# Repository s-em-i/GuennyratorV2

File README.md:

# GuennyratorV2

## Status
* In development

## License
* No License, open domain

## Johnson Counter (Train)
* [Texas Instruments CD74ACT175 Quad D-Type Flip-Flops with Reset](https://www.ti.com/product/CD74ACT175)
* [CMOS Dual J-K Master-Slave Flip-Flop](https://www.ti.com/product/CD4027B)

## Ring Counter
* [Texas Instruments CD74HC4017 High Speed CMOS Logic Decade Counter/Divider with 10 Decoded Outputs](https://www.ti.com/product/CD74HC4017)

## Direction Change
* [Texas Instruments CD74AC00 4-ch, 2-input, 1.5-V to 5.5-V NAND gates](https://www.ti.com/product/CD74AC00)

## Square Wave with 50% accurate Duty Cycle Frequency Generator
* [Texas Instruments TLC555 2.1-MHz, 250-µA, Low-Power Timer](https://www.ti.com/product/TLC555)

## Mechanical Setup
* [STATOR TRIUMPH 955(i)](https://www.rmstator-europe.com/en/955-tiger-/310-stator-triumph-speed-triple-955-sprint-rs-955-sprint-st-955-tiger-955-oem-t1300502-t1300350.html)
	- Dimensions :
		- Interior diameter : 41 mm 
		- Exterior diameter : 104 mm 
		- Thickness : 22 mm
* [AS-PL Alternator stator AS2002](https://as-pl.com/en/p/AS2002)
	- Dimensions :
		- I.D.1 [ mm ]	104.30
		- H.2 [ mm ]	22.10
* [AS-PL Alternator A2005](https://as-pl.com/en/p/A2005)

## Signalgenerator (PLL)
* [XR2206 Multi-Function Generator](https://www.uctronics.com/download/Amazon/U6035.pdf)
* [ICL8038](https://www.delabs-circuits.com/cirdir/hobby/test-tools/del50005.html)
* [Texas Instruments CD4060B CMOS 14-Stage Ripple-Carry Binary Counter/Divider and Oscillator](https://www.ti.com/product/CD4060B)
* [Texas Instruments SN74HC4060-Q1 ACTIVE Automotive Catalog 14-Stage Asynchronous Binary Counters And Oscillators](https://www.ti.com/product/SN74HC4060-Q1)

### Credits
* [Schematics Simulated with Analog Devices LTspice](https://www.analog.com/en/design-center/design-tools-and-calculators/ltspice-simulator.html)
* [Schematics Designed with KiCad EDA](https://www.kicad.org)
* [USING CD4000_V.LIB AND 74HC.LIB IN LTSPICE by acidbourbon](https://acidbourbon.wordpress.com/2021/06/30/using-cd4000_v-lib-in-ltspice/)
* [Logisim by carlburch](https://sourceforge.net/projects/circuit/)
* [TEXMAKER - LaTex](https://www.xm1math.net/texmaker/download.html)
* [Alexander Baran-Harper - Latex Tutorials](https://www.youtube.com/watch?v=FXujG7c9p8g&list=PLNnwglGGYoTtW7o4PHFOSWGevcdFa3v3D)
* [Michelle Krummel  - Latex Tutorials](https://www.youtube.com/watch?v=0ivLZh9xK1Q&list=PL1D4EAB31D3EBC449)

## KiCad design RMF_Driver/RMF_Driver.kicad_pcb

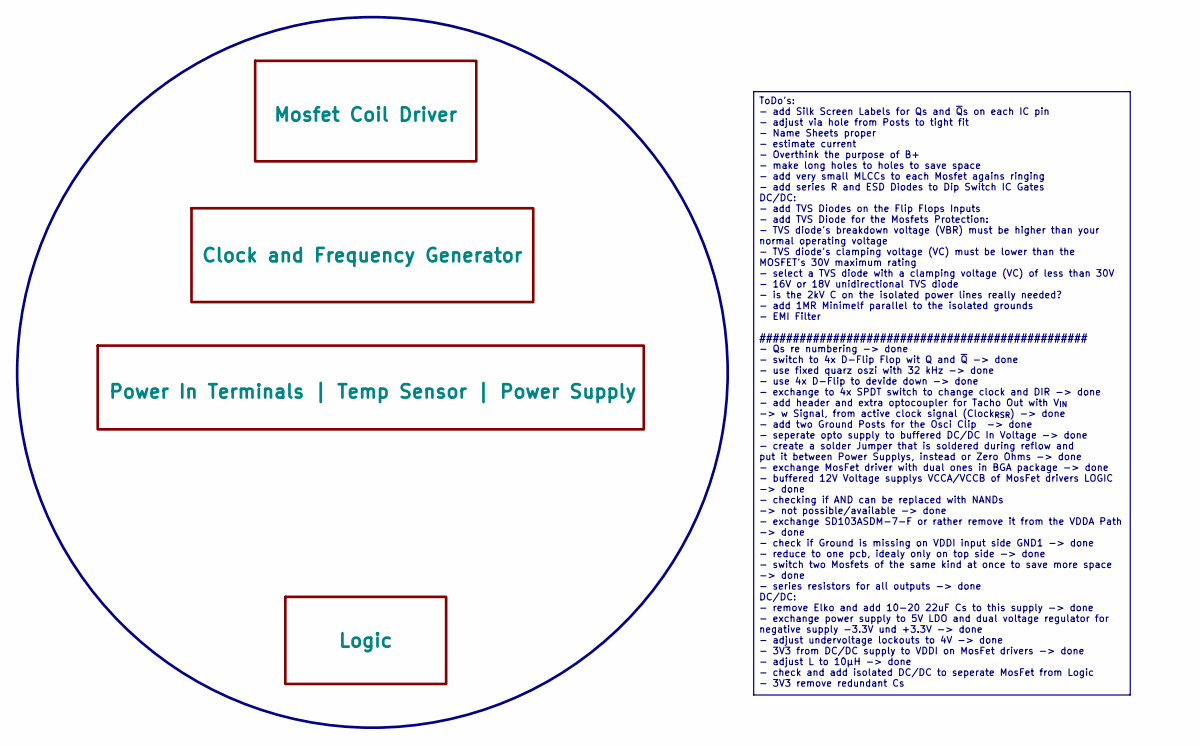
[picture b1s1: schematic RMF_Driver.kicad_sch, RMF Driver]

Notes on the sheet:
ToDo's: - add Silk Screen Labels for Qs and ~{Q}s on each IC pin - adjust via hole from Posts to tight fit - Name Sheets proper - estimate current - Overthink the purpose of B+ - make long holes to holes to save space - add very small MLCCs to each Mosfet agains ringing - add series R and ESD Diode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

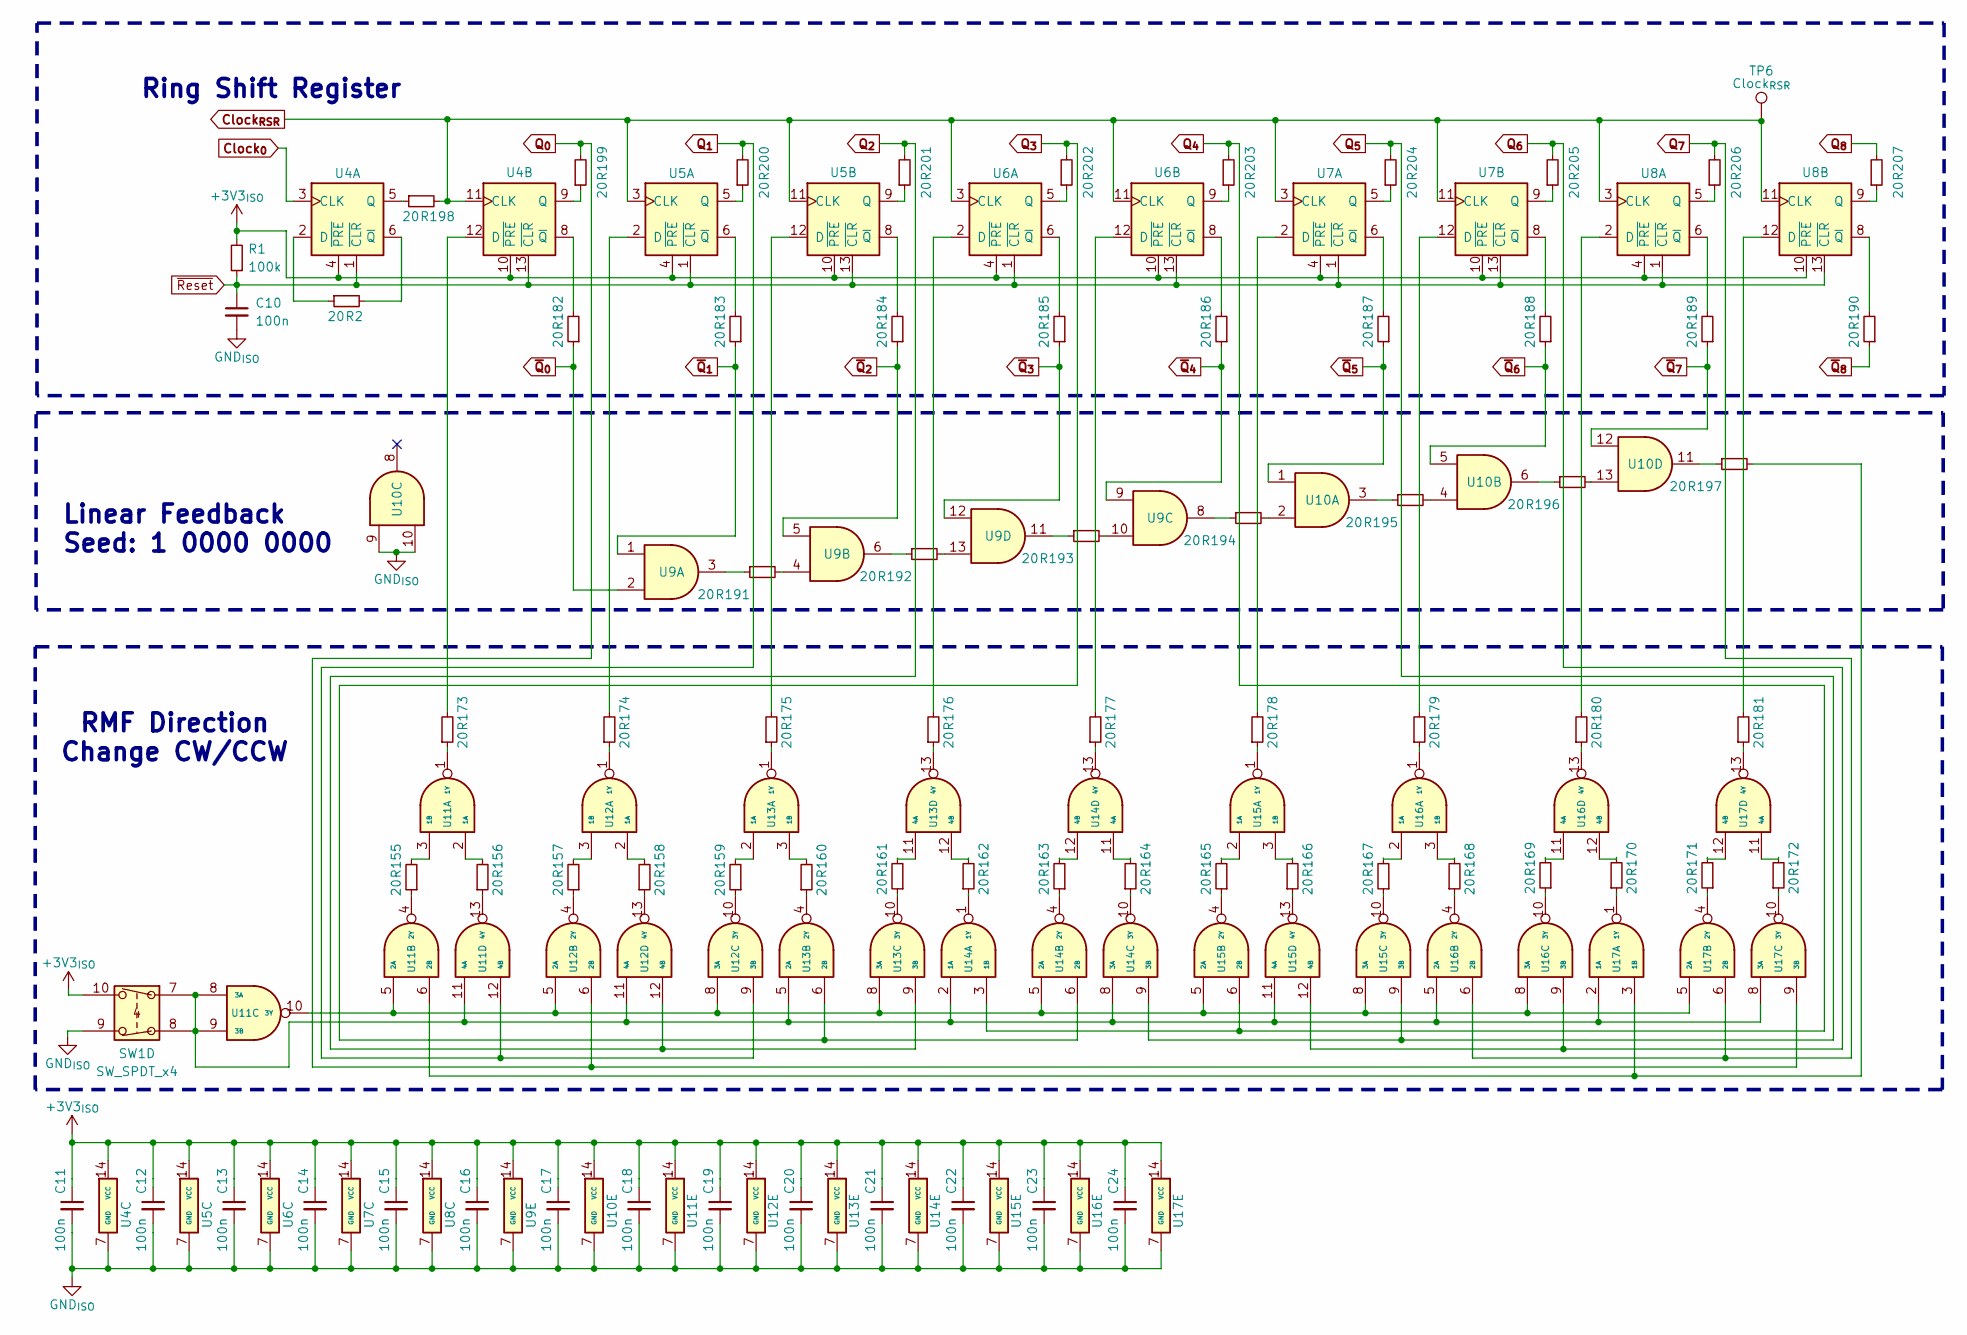
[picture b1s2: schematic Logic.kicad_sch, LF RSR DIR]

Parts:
C10, C11, C12, C13, C14, C15, C16, C17, C18, C19, C20, C21, C22, C23, C24: 100n; C_0402_1005Metric; MPN 1 CL05B104KB54PNC
R1: 100k; R_0402_1005Metric; MPN 1 AC0402FR-13100KL
R2, R155, R156, R157, R158, R159, R160, R161, R162, R163, R164, R165, R166, R167, R168, R169, R170, R171, R172, R173, R174, R175, R176, R177, R178, R179, R180, R181, R182, R183, R184, R185, R186, R187, R188, R189, R190, R191, R192, R193, R194, R195, R196, R197, R198, R199, R200, R201, R202, R203, R204, R205, R206, R207: 20; R_0402_1005Metric; MPN 1 AC0402FR-0720RL
SW1: SW_SPDT_x4; CTS_204-124; MPN 1 204-124LPST
TP6: Clock_{RSR}; 243-131; MPN 1 243-131
U4, U5, U6, U7, U8: D-FF; DHVQFN-14-1EP_2.5x3mm_P0.5mm_EP1x1.5mm
U9, U10: AND; WQFN-14-1EP_2.6x3.1mm_P0.5mm_EP1.1x1.6mm_ThermalVias; MPN 1 SN74AHC08QWBQARQ1
U11, U12, U13, U14, U15, U16, U17: NAND; WQFN-14-1EP_2.6x3.1mm_P0.5mm_EP1.1x1.6mm_ThermalVias; MPN 1 SN74AHC00BQAR

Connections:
+3V3_{ISO}: C11.1, C12.1, C13.1, C14.1, C15.1, C16.1, C17.1, C18.1, C19.1, C20.1, C21.1, C22.1, C23.1, C24.1, R1.2, SW1.10 (D), U4.4 (~PRE), U4.10 (~PRE), U4.14 (VCC), U5.4 (~PRE), U5.10 (~PRE), U5.14 (VCC), U6.4 (~PRE), U6.10 (~PRE), U6.14 (VCC), U7.4 (~PRE), U7.10 (~PRE), U7.14 (VCC), U8.4 (~PRE), U8.10 (~PRE), U8.14 (VCC), U9.14 (VCC), U10.14 (VCC), U11.14 (VCC), U12.14 (VCC), U13.14 (VCC), U14.14 (VCC), U15.14 (VCC), U16.14 (VCC), U17.14 (VCC); also elsewhere on the board
Clock_{0}: U4.3 (CLK); also elsewhere on the board
Clock_{RSR}: R198.2, TP6.1 (1_1), U4.11 (CLK), U5.3 (CLK), U5.11 (CLK), U6.3 (CLK), U6.11 (CLK), U7.3 (CLK), U7.11 (CLK), U8.3 (CLK), U8.11 (CLK); also elsewhere on the board
GND_{ISO}: C10.2, C11.2, C12.2, C13.2, C14.2, C15.2, C16.2, C17.2, C18.2, C19.2, C20.2, C21.2, C22.2, C23.2, C24.2, SW1.9 (C), U4.7 (GND), U4.15 (PAD), U5.7 (GND), U5.15 (PAD), U6.7 (GND), U6.15 (PAD), U7.7 (GND), U7.15 (PAD), U8.7 (GND), U8.15 (PAD), U9.7 (GND), U9.15 (GND), U10.7 (GND), U10.9, U10.10, U10.15 (GND), U11.7 (GND), U11.15 (GND), U12.7 (GND), U12.15 (GND), U13.7 (GND), U13.15 (GND), U14.7 (GND), U14.15 (GND), U15.7 (GND), U15.15 (GND), U16.7 (GND), U16.15 (GND), U17.7 (GND), U17.15 (GND); also elsewhere on the board
unnamed: R191.1, U9.3
unnamed: R191.2, U9.4
unnamed: R192.1, U9.6
unnamed: R192.2, U9.13
unnamed: R193.1, U9.11
unnamed: R193.2, U9.10
unnamed: R194.1, U9.8
unnamed: R194.2, U10.2
unnamed: R195.1, U10.3
unnamed: R195.2, U10.4
unnamed: R196.1, U10.6
unnamed: R196.2, U10.13
unnamed: R197.1, U10.11
unnamed: SW1.7 (A), SW1.8 (B), U11.8 (3A), U11.9 (3B), U11.11 (4A), U12.11 (4A), U13.5 (2A), U14.2 (1A), U14.8 (3A), U15.11 (4A), U16.5 (2A), U17.2 (1A), U17.8 (3A)
unnamed: R2.1, U4.2 (D)
unnamed: R198.1, U4.5 (Q)
unnamed: R2.2, U4.6 (~Q)
unnamed: R173.2, U4.12 (D)
unnamed: R199.1, U4.9 (Q)
unnamed: R182.2, U4.8 (~Q)
unnamed: R174.2, U5.2 (D)
unnamed: R200.1, U5.5 (Q)
unnamed: R183.2, U5.6 (~Q)
unnamed: R175.2, U5.12 (D)
unnamed: R201.1, U5.9 (Q)
unnamed: R184.2, U5.8 (~Q)
unnamed: R176.2, U6.2 (D)
unnamed: R202.1, U6.5 (Q)
unnamed: R185.2, U6.6 (~Q)
unnamed: R177.2, U6.12 (D)
unnamed: R203.1, U6.9 (Q)
unnamed: R186.2, U6.8 (~Q)
unnamed: R178.2, U7.2 (D)
unnamed: R204.1, U7.5 (Q)
unnamed: R187.2, U7.6 (~Q)
unnamed: R179.2, U7.12 (D)
unnamed: R205.1, U7.9 (Q)
unnamed: R188.2, U7.8 (~Q)
unnamed: R180.2, U8.2 (D)
unnamed: R206.1, U8.5 (Q)
unnamed: R189.2, U8.6 (~Q)
unnamed: R181.2, U8.12 (D)
unnamed: R207.1, U8.9 (Q)
unnamed: R190.2, U8.8 (~Q)
unnamed: R156.2, U11.2 (1A)
unnamed: R155.2, U11.3 (1B)
unnamed: R173.1, U11.1 (1Y)
unnamed: U11.5 (2A), U11.10 (3Y), U12.5 (2A), U12.8 (3A), U13.8 (3A), U14.5 (2A), U15.5 (2A), U15.8 (3A), U16.8 (3A), U17.5 (2A)
unnamed: R197.2, U11.6 (2B), U17.3 (1B)
unnamed: R155.1, U11.4 (2Y)
unnamed: R156.1, U11.13 (4Y)
unnamed: R158.2, U12.2 (1A)
unnamed: R157.2, U12.3 (1B)
unnamed: R174.1, U12.1 (1Y)
unnamed: R157.1, U12.4 (2Y)
unnamed: R159.1, U12.10 (3Y)
unnamed: R158.1, U12.13 (4Y)
unnamed: R159.2, U13.2 (1A)
unnamed: R160.2, U13.3 (1B)
unnamed: R175.1, U13.1 (1Y)
unnamed: R160.1, U13.4 (2Y)
unnamed: R161.1, U13.10 (3Y)
unnamed: R161.2, U13.11 (4A)
unnamed: R162.2, U13.12 (4B)
unnamed: R176.1, U13.13 (4Y)
unnamed: R162.1, U14.1 (1Y)
unnamed: R163.1, U14.4 (2Y)
unnamed: R164.1, U14.10 (3Y)
unnamed: R164.2, U14.11 (4A)
unnamed: R163.2, U14.12 (4B)
unnamed: R177.1, U14.13 (4Y)
unnamed: R165.2, U15.2 (1A)
unnamed: R166.2, U15.3 (1B)
unnamed: R178.1, U15.1 (1Y)
unnamed: R165.1, U15.4 (2Y)
unnamed: R167.1, U15.10 (3Y)
unnamed: R166.1, U15.13 (4Y)
unnamed: R167.2, U16.2 (1A)
unnamed: R168.2, U16.3 (1B)
unnamed: R179.1, U16.1 (1Y)
unnamed: R168.1, U16.4 (2Y)
unnamed: R169.1, U16.10 (3Y)
unnamed: R169.2, U16.11 (4A)
unnamed: R170.2, U16.12 (4B)
unnamed: R180.1, U16.13 (4Y)
unnamed: R170.1, U17.1 (1Y)
unnamed: R171.1, U17.4 (2Y)
unnamed: R172.1, U17.10 (3Y)
unnamed: R172.2, U17.11 (4A)
unnamed: R171.2, U17.12 (4B)
unnamed: R181.1, U17.13 (4Y)
Q_{0}: R199.2, U12.6 (2B), U17.9 (3B); also elsewhere on the board
Q_{1}: R200.2, U11.12 (4B), U12.9 (3B); also elsewhere on the board
Q_{2}: R201.2, U12.12 (4B), U13.9 (3B); also elsewhere on the board
Q_{3}: R202.2, U13.6 (2B), U14.6 (2B); also elsewhere on the board
Q_{4}: R203.2, U14.3 (1B), U15.6 (2B); also elsewhere on the board
Q_{5}: R204.2, U14.9 (3B), U15.9 (3B); also elsewhere on the board
Q_{6}: R205.2, U15.12 (4B), U16.9 (3B); also elsewhere on the board
Q_{7}: R206.2, U16.6 (2B), U17.6 (2B); also elsewhere on the board
Q_{8}: R207.2; also elsewhere on the board
~Q_{0}: R182.1, U9.2; also elsewhere on the board
~Q_{1}: R183.1, U9.1; also elsewhere on the board
~Q_{2}: R184.1, U9.5; also elsewhere on the board
~Q_{3}: R185.1, U9.12; also elsewhere on the board
~Q_{4}: R186.1, U9.9; also elsewhere on the board
~Q_{5}: R187.1, U10.1; also elsewhere on the board
~Q_{6}: R188.1, U10.5; also elsewhere on the board
~Q_{7}: R189.1, U10.12; also elsewhere on the board
~Q_{8}: R190.1; also elsewhere on the board
~Reset: C10.1, R1.1, U4.1 (~CLR), U4.13 (~CLR), U5.1 (~CLR), U5.13 (~CLR), U6.1 (~CLR), U6.13 (~CLR), U7.1 (~CLR), U7.13 (~CLR), U8.1 (~CLR), U8.13 (~CLR); also elsewhere on the board

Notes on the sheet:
Ring Shift Register
RMF Direction Change CW/CCW
Linear Feedback Seed: 1 0000 0000

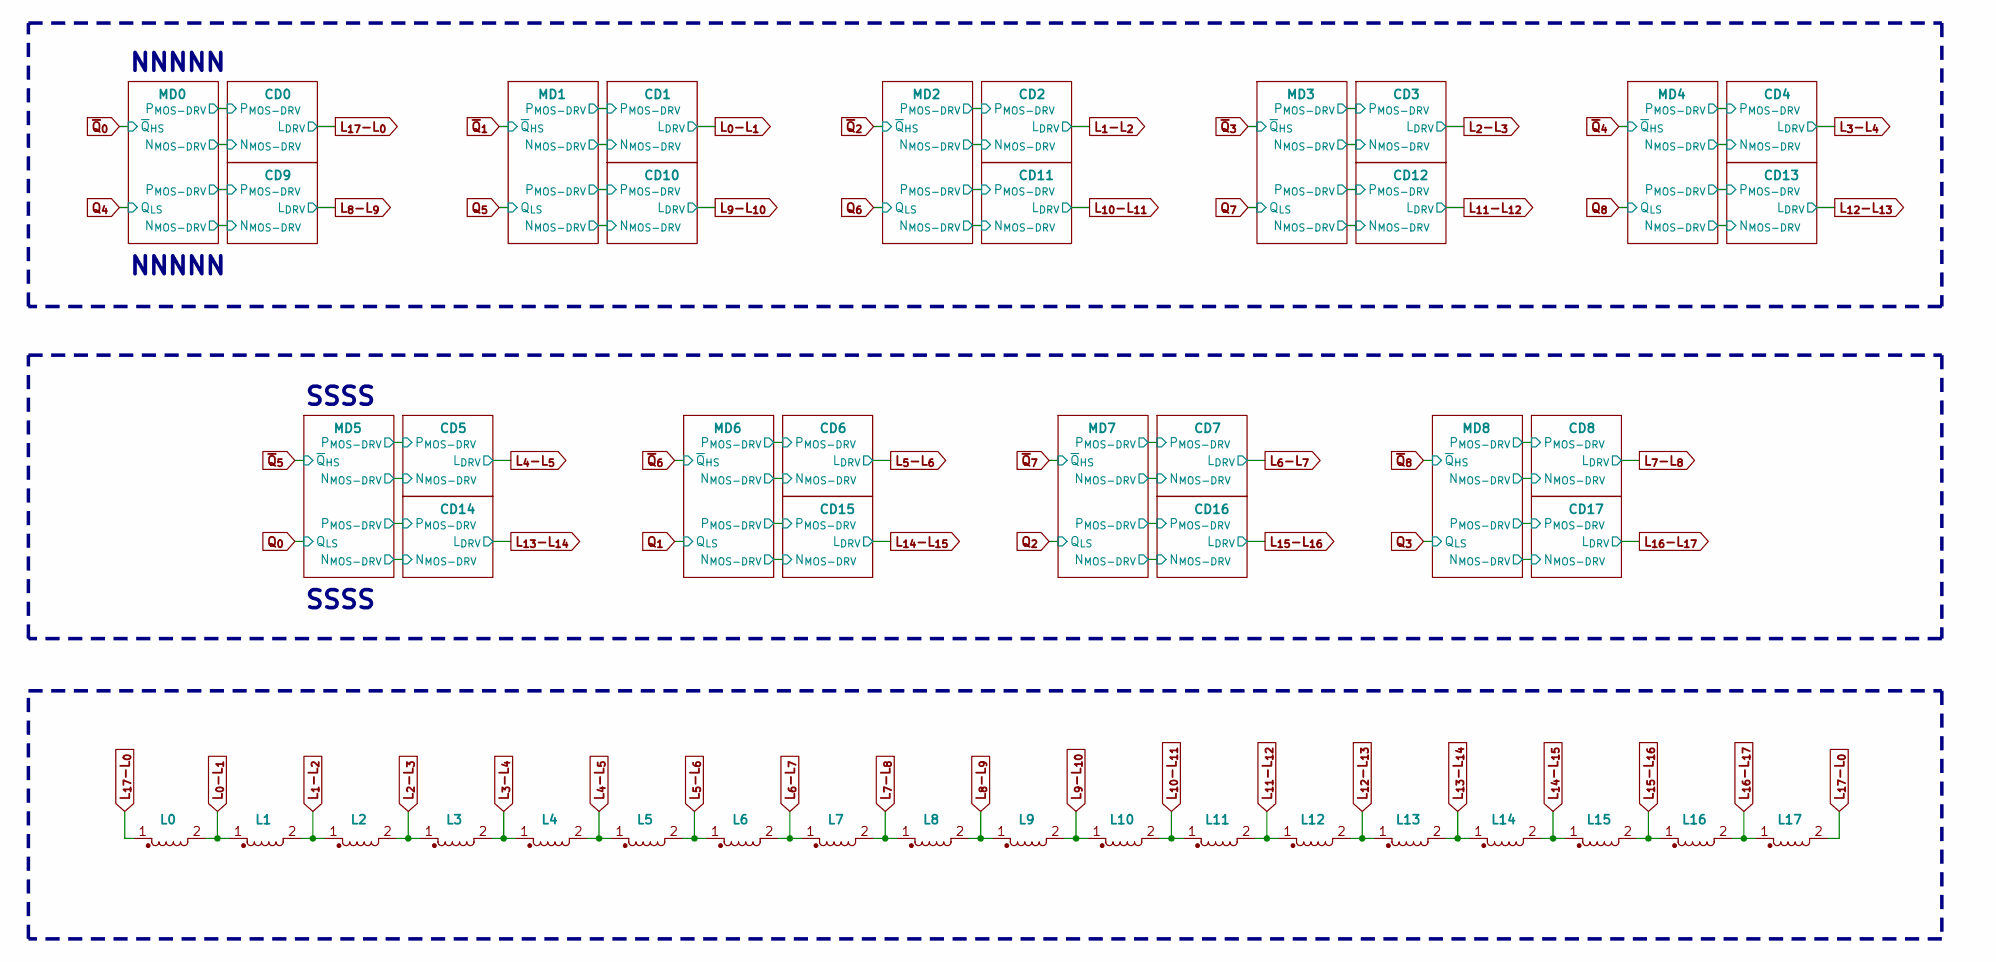
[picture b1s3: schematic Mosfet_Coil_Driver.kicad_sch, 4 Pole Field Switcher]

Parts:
L0, L1, L2, L3, L4, L5, L6, L7, L8, L9, L10, L11, L12, L13, L14, L15, L16, L17: L

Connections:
unnamed: L0.1, L17.2
unnamed: L0.2, L1.1
unnamed: L1.2, L2.1
unnamed: L2.2, L3.1
unnamed: L3.2, L4.1
unnamed: L4.2, L5.1
unnamed: L5.2, L6.1
unnamed: L6.2, L7.1
unnamed: L7.2, L8.1
unnamed: L8.2, L9.1
unnamed: L9.2, L10.1
unnamed: L10.2, L11.1
unnamed: L11.2, L12.1
unnamed: L12.2, L13.1
unnamed: L13.2, L14.1
unnamed: L14.2, L15.1
unnamed: L15.2, L16.1
unnamed: L16.2, L17.1

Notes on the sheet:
NNNNN
SSSS

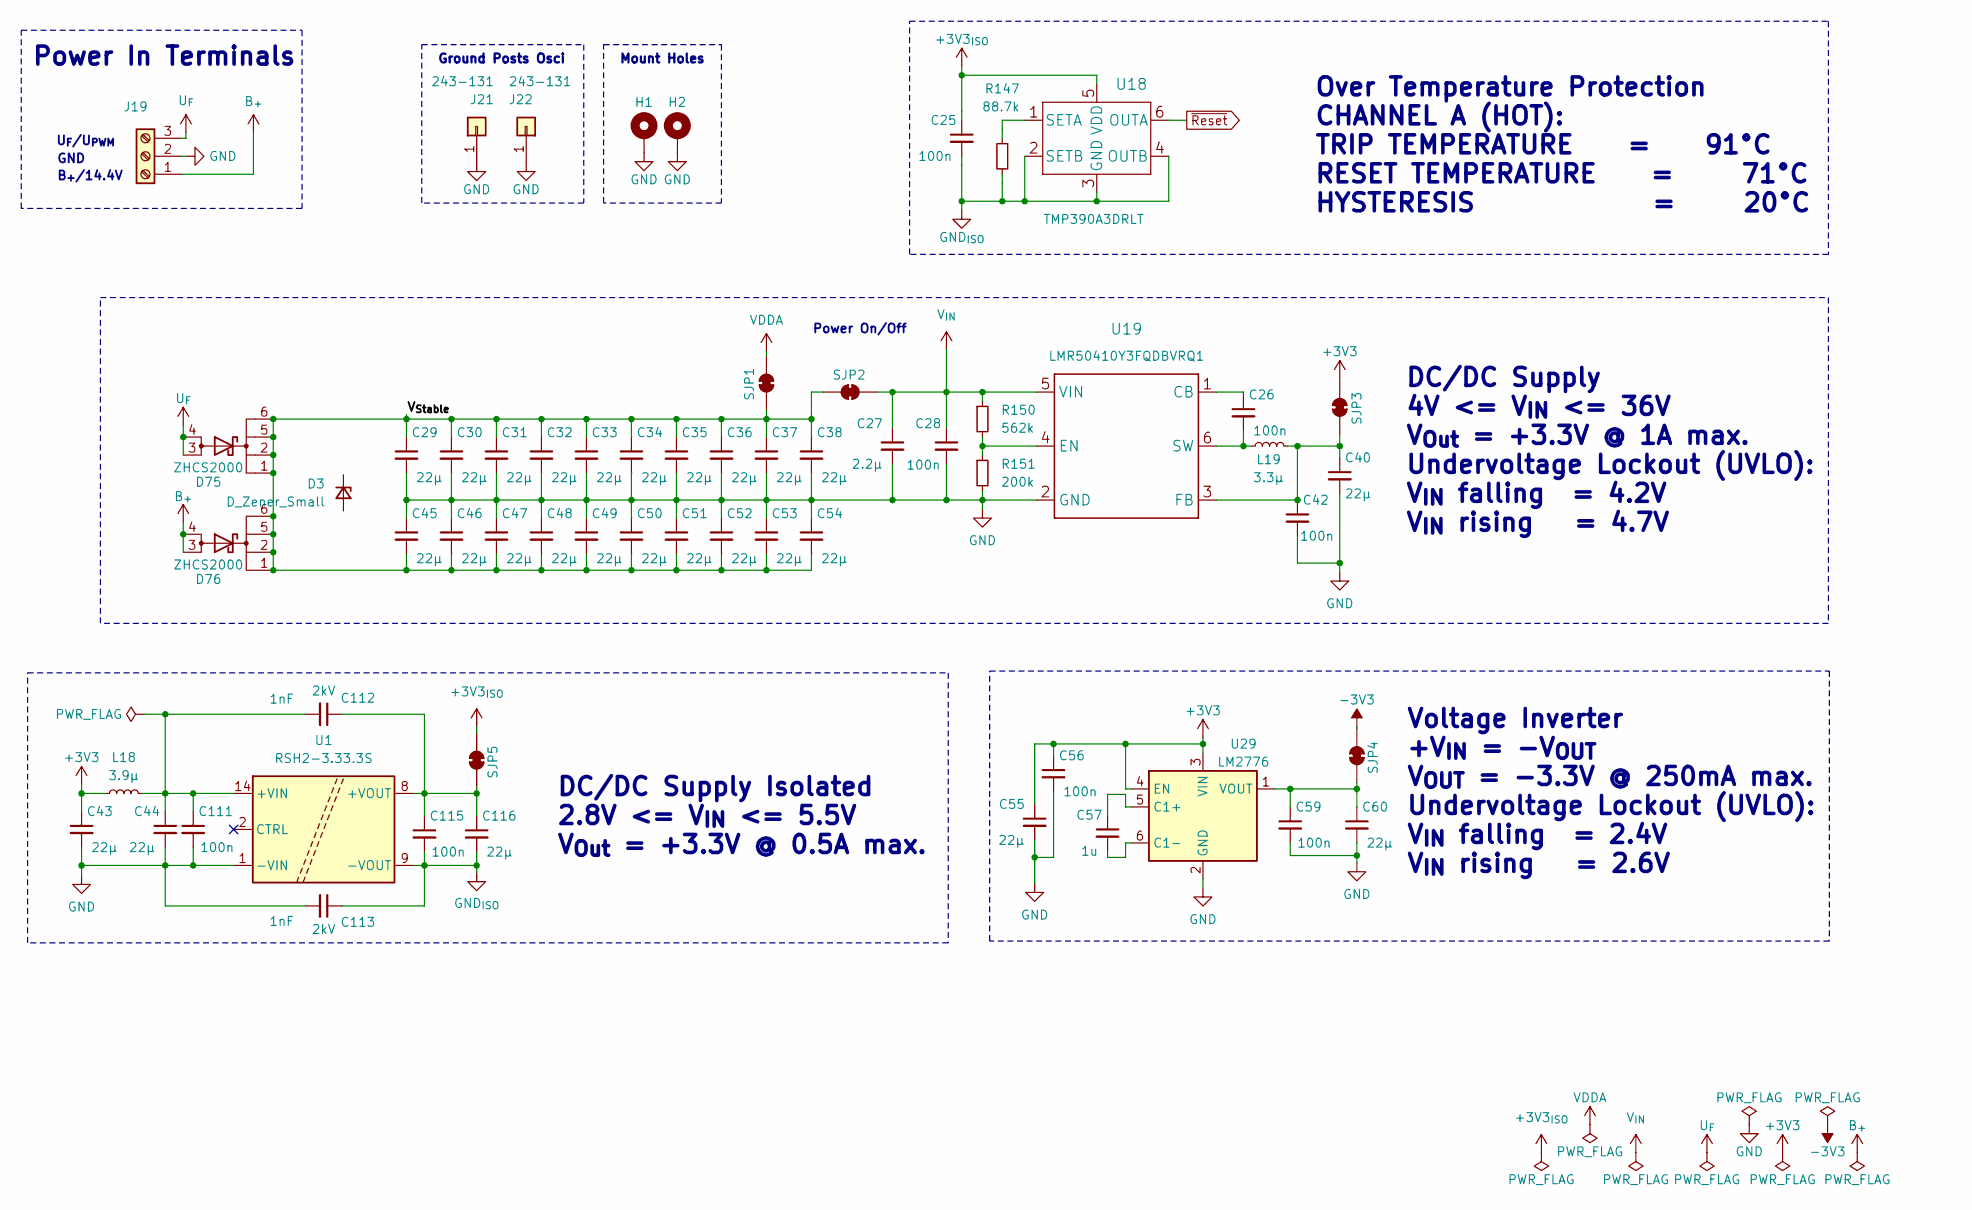
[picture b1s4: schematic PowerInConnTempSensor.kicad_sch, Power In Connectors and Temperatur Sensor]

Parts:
C25, C26, C28, C42, C56, C59, C111, C115: 100n; C_0402_1005Metric; MPN 1 CL05B104KB54PNC
C27: 2.2µ; C_0805_2012Metric; MPN 1 CL21B225KBYNNWE
C29, C30, C31, C32, C33, C34, C35, C36, C37, C38, C45, C46, C47, C48, C49, C50, C51, C52, C53, C54: 22µ; C_1210_3225Metric; MPN 1 CL32B226KAJNNNE
C40, C43, C44, C55, C60, C116: 22µ; C_0805_2012Metric; MPN 1 GRM21BZ71A226ME15L
C57: 1u; C_0603_1608Metric; MPN 1 CL10B105KB8NQNC
C112, C113: 1nF; C_1206_3216Metric; Voltage 2kV; MPN 1 C1206C102KGRAC
D3: D_Zener_Small
D75, D76: ZHCS2000; SOT-23-6; MPN 1 ZHCS2000
H1, H2: MountingHole_Pad; MountingHole_6.4mm_M6_ISO7380_Pad_TopBottom
J19: Screw_Terminal_01x03; PHOENIX_1984950; MPN 1 1984950
J21, J22: 243-131; MPN 1 243-131
L18: 3.9µ; L_Recom_RLS-397_4.5x3.2mm; MPN 1 RLS-397
L19: 3.3µ; WE-LHMI_4020; MPN 1 74437324033
R147: 88.7k; R_0603_1608Metric; MPN 1 RC0603FR-0788K7L
R150: 562k; R_0603_1608Metric; MPN 1 RC0603FR-07562KL
R151: 200k; R_0603_1608Metric; MPN 1 AC0603FR-07200KL
SJP1, SJP2, SJP3, SJP4, SJP5: SolderJumper_2_Bridged; SolderJumper-2_P1.3mm_Open_TrianglePad1.0x1.5mm
U1: RSH2-3.33.3S; RSH2; MPN 1 RSH2-3.33.3S
U18: TMP390A3DRLT; MPN 1 TMP390A3DRLT
U19: LMR50410Y3FQDBVRQ1; PLMR50410XDBVR; MPN 1 LMR50410Y3FQDBVRQ1
U29: LM2776; SOT-23-6

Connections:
+3V3: C43.1, C55.1, C56.1, L18.1, SJP3.2 (B), U29.3 (VIN), U29.4 (EN)
+3V3_{ISO}: C25.1, SJP5.2 (B), U18.5 (VDD); also elsewhere on the board
-3V3: SJP4.2 (B); also elsewhere on the board
/Power In Terminals | Temp Sensor | Power Supply/V_{Stable}: C29.1, C30.1, C31.1, C32.1, C33.1, C34.1, C35.1, C36.1, C37.1, C38.1, C45.2, C46.2, C47.2, C48.2, C49.2, C50.2, C51.2, C52.2, C53.2, C54.2, D75.1 (K), D75.2 (K), D75.5 (K), D75.6 (K), D76.1 (K), D76.2 (K), D76.5 (K), D76.6 (K), SJP1.1 (A), SJP2.1 (A)
B_{+}: D76.3 (A), D76.4 (A), J19.1
GND: C27.2, C28.2, C29.2, C30.2, C31.2, C32.2, C33.2, C34.2, C35.2, C36.2, C37.2, C38.2, C40.2, C42.2, C43.2, C44.2, C45.1, C46.1, C47.1, C48.1, C49.1, C50.1, C51.1, C52.1, C53.1, C54.1, C55.2, C56.2, C59.2, C60.2, C111.2, C113.2, H1.1 (1_1), H2.1 (1_1), J19.2, J21.1 (Pin_1_1), J22.1 (Pin_1_1), R151.2, U1.1 (-VIN), U1.6 (-VIN), U1.7 (-VIN), U19.2 (GND), U29.2 (GND); also elsewhere on the board
GND_{ISO}: C25.2, C113.1, C115.2, C116.2, R147.2, U1.9 (-VOUT), U18.2 (SETB), U18.3 (GND), U18.4 (OUTB); also elsewhere on the board
unnamed: C40.1, C42.1, L19.1, SJP3.1 (A), U19.3 (FB)
unnamed: C59.1, C60.1, SJP4.1 (A), U29.1 (VOUT)
unnamed: C112.1, C115.1, C116.1, SJP5.1 (A), U1.8 (+VOUT)
unnamed: C44.1, C111.1, C112.2, L18.2, U1.14 (+VIN)
unnamed: R147.1, U18.1 (SETA)
unnamed: C26.1, U19.1 (CB)
unnamed: R150.2, R151.1, U19.4 (EN)
unnamed: C26.2, L19.2, U19.6 (SW)
unnamed: C57.1, U29.5 (C1+)
unnamed: C57.2, U29.6 (C1-)
U_{F}: D75.3 (A), D75.4 (A), J19.3; also elsewhere on the board
VDDA: SJP1.2 (B); also elsewhere on the board
V_{IN}: C27.1, C28.1, R150.1, SJP2.2 (B), U19.5 (VIN)
~Reset: U18.6 (OUTA); also elsewhere on the board

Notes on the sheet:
Power On/Off
Power In Terminals
Over Temperature Protection CHANNEL A (HOT): TRIP TEMPERATURE = 91°C RESET TEMPERATURE = 71°C HYSTERESIS = 20°C
DC/DC Supply 4V <= V_{IN} <= 36V V_{Out} = +3.3V @ 1A max. Undervoltage Lockout (UVLO): V_{IN} falling = 4.2V V_{IN} rising = 4.7V
Mount Holes
Voltage Inverter +V_{IN} = -V_{OUT} V_{OUT} = -3.3V @ 250mA max. Undervoltage Lockout (UVLO): V_{IN} falling = 2.4V V_{IN} rising = 2.6V
DC/DC Supply Isolated 2.8V <= V_{IN} <= 5.5V V_{Out} = +3.3V @ 0.5A max.
GND
Ground Posts Osci
U_{F}/U_{PWM}
B_{+}/14.4V

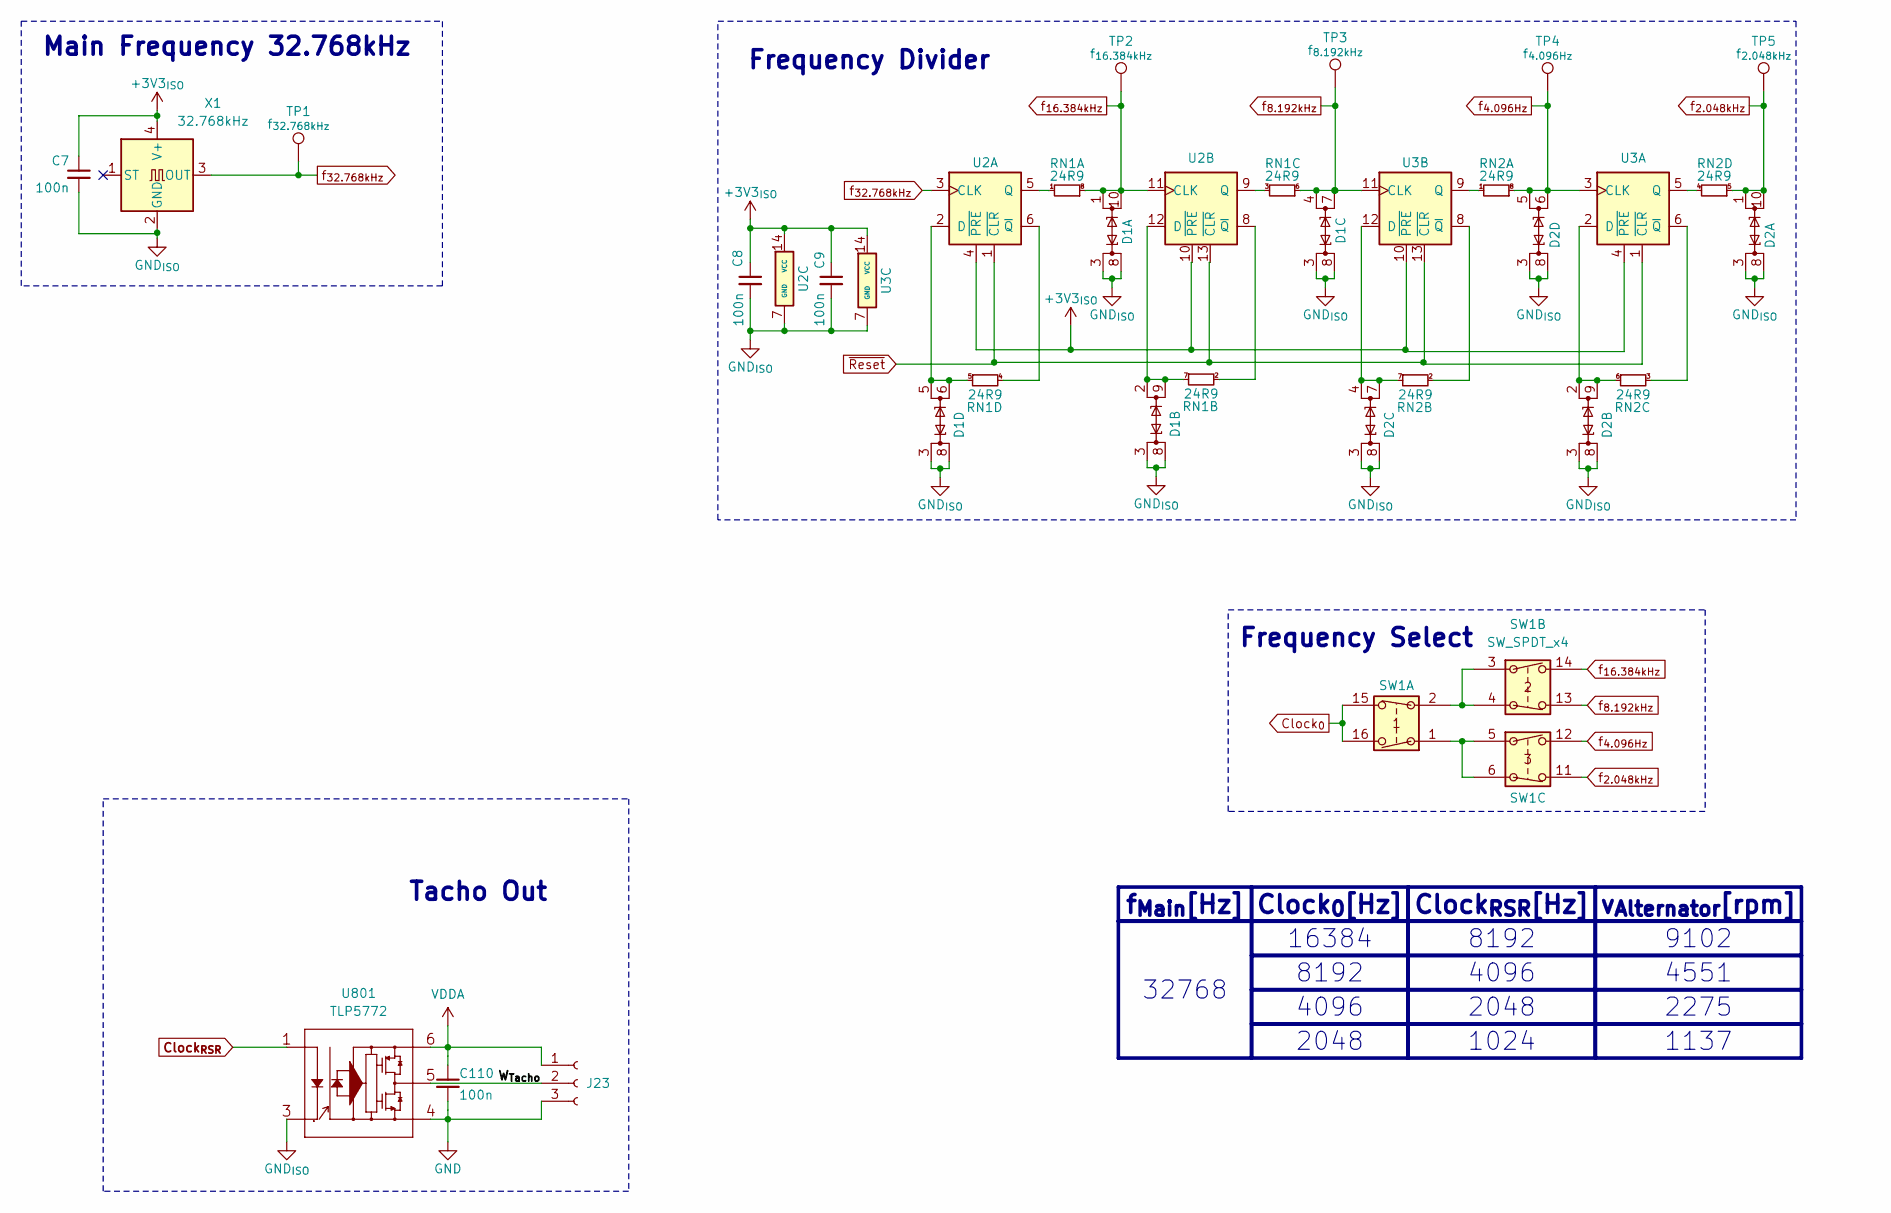
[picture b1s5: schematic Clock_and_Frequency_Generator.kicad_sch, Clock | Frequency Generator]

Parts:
C7, C8, C9, C110: 100n; C_0402_1005Metric; MPN 1 CL05B104KB54PNC
D1, D2: PUSB3BB4Z; Diodes_DFN2510A-10_1.1x2.6mm_P0.5mm; MPN 1 PUSB3BB4Z
J23: Conn_01x03_Socket; PinHeader_1x03_P2.54mm_Vertical
RN1, RN2: 24R9; R_Cat16-4; MPN 1 CAY16-24R9F4LF
SW1: SW_SPDT_x4; CTS_204-124; MPN 1 204-124LPST
TP1: f_{32.768kHz}; 243-131; MPN 1 243-131
TP2: f_{16.384kHz}; 243-131; MPN 1 243-131
TP3: f_{8.192kHz}; 243-131; MPN 1 243-131
TP4: f_{4.096Hz}; 243-131; MPN 1 243-131
TP5: f_{2.048kHz}; 243-131; MPN 1 243-131
U2, U3: D-FF; DHVQFN-14-1EP_2.5x3mm_P0.5mm_EP1x1.5mm
U801: TLP5772
X1: 32.768kHz; Oscillator_SMD_IQD_QXO-40x-4Pin_2.0x1.6mm; MPN 1 LFSPXO073701Reel

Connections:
+3V3_{ISO}: C7.1, C8.1, C9.1, U2.4 (~PRE), U2.10 (~PRE), U2.14 (VCC), U3.4 (~PRE), U3.10 (~PRE), U3.14 (VCC), X1.4 (V+); also elsewhere on the board
/Clock and Frequency Generator/W_{Tacho}: J23.2, U801.5 (VO)
Clock_{0}: SW1.15 (C), SW1.16 (D); also elsewhere on the board
Clock_{RSR}: U801.1 (ANODE); also elsewhere on the board
GND: C110.2, J23.3, U801.4 (GND); also elsewhere on the board
GND_{ISO}: C7.2, C8.2, C9.2, D1.3 (GND), D1.8 (GND), D2.3 (GND), D2.8 (GND), U2.7 (GND), U2.15 (PAD), U3.7 (GND), U3.15 (PAD), U801.3 (CATHODE), X1.2 (GND); also elsewhere on the board
unnamed: RN1.1 (R1.1), U2.5 (Q)
unnamed: RN1.2 (R2.1), U2.8 (~Q)
unnamed: D1.2 (CH2), D1.9 (CH2), RN1.7 (R2.2), U2.12 (D)
unnamed: RN1.3 (R3.1), U2.9 (Q)
unnamed: RN1.4 (R4.1), U2.6 (~Q)
unnamed: D1.5 (CH4), D1.6 (CH4), RN1.5 (R4.2), U2.2 (D)
unnamed: RN2.1 (R1.1), U3.9 (Q)
unnamed: RN2.2 (R2.1), U3.8 (~Q)
unnamed: D2.4 (CH3), D2.7 (CH3), RN2.7 (R2.2), U3.12 (D)
unnamed: RN2.3 (R3.1), U3.6 (~Q)
unnamed: D2.2 (CH2), D2.9 (CH2), RN2.6 (R3.2), U3.2 (D)
unnamed: RN2.4 (R4.1), U3.5 (Q)
unnamed: SW1.1 (A), SW1.5 (A), SW1.6 (B)
unnamed: SW1.2 (B), SW1.3 (A), SW1.4 (B)
VDDA: C110.1, J23.1, U801.6 (VCC); also elsewhere on the board
f_{2.048kHz}: D2.1 (CH1), D2.10 (CH1), RN2.5 (R4.2), SW1.11 (C), TP5.1 (1_1)
f_{4.096Hz}: D2.5 (CH4), D2.6 (CH4), RN2.8 (R1.2), SW1.12 (D), TP4.1 (1_1), U3.3 (CLK)
f_{8.192kHz}: D1.4 (CH3), D1.7 (CH3), RN1.6 (R3.2), SW1.13 (C), TP3.1 (1_1), U3.11 (CLK)
f_{16.384kHz}: D1.1 (CH1), D1.10 (CH1), RN1.8 (R1.2), SW1.14 (D), TP2.1 (1_1), U2.11 (CLK)
f_{32.768kHz}: TP1.1 (1_1), U2.3 (CLK), X1.3 (OUT)
~Reset: U2.1 (~CLR), U2.13 (~CLR), U3.1 (~CLR), U3.13 (~CLR); also elsewhere on the board

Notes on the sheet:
Frequency Divider
Frequency Select
Tacho Out
Main Frequency 32.768kHz
1137
4096
2048
8192
1024
16384
9102
32768
v_{Alternator}[rpm]
Clock_{0}[Hz]
Clock_{RSR}[Hz]
4551
f_{Main}[Hz]
2275
